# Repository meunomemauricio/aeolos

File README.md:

# Aeolus

Arduino PWM Fan Controller.

## Uploading Firmware

This projects use Platform IO. When building or uploading the firmware, it's
important to specify the build environment. This will set the proper
`MODULE_ID` value depending on the expected fan direction.

    pio run -e exhaust -t upload
    pio run -e intake -t upload

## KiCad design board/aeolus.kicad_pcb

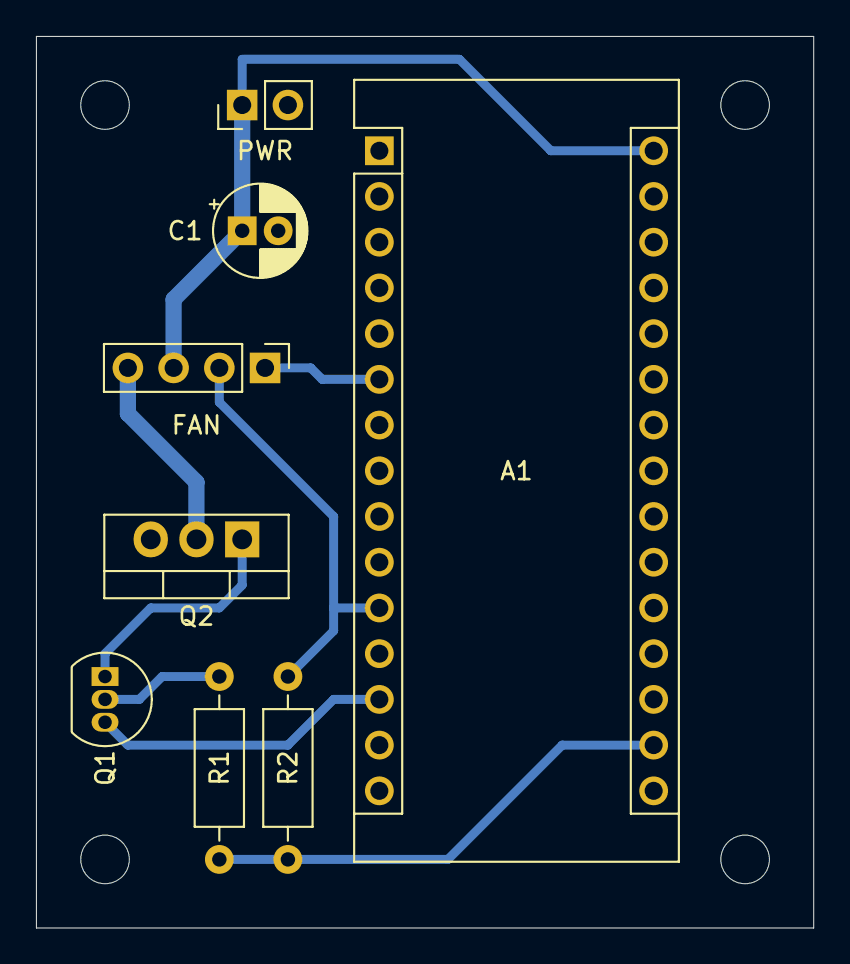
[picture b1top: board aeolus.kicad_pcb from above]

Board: 2 copper layers, 43.2 x 49.5 mm, 8 parts (0 on the bottom side), 9 nets.

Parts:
A1: Arduino_Nano_v2.x; Arduino_Nano
C1: 1uF; CP_Radial_D5.0mm_P2.00mm
FAN: Conn_01x04_Male; PinHeader_1x04_P2.54mm_Vertical
PWR: Conn_01x02_Male; PinHeader_1x02_P2.54mm_Vertical
Q1: BC549; TO-92_Inline
Q2: IRF540N; TO-220-3_Vertical
R1, R2: 10k; R_Axial_DIN0207_L6.3mm_D2.5mm_P10.16mm_Horizontal

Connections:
+3V3: A1.17, R1.1, R2.1
+12V: A1.30, C1.1, FAN.3, PWR.1
/FAN_GND: FAN.4, Q2.2
/PWM: A1.6, FAN.1
/TACH: A1.11, FAN.2, R2.2
GND: A1.29, C1.2, PWR.2, Q2.3
unnamed: A1.13, Q1.3
unnamed: Q1.1, Q2.1
unnamed: Q1.2, R1.2

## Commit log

2022-02-17 Extract from other repository
2022-02-18 Rename board and create SCAD file
2022-02-18 Project basic Setup (#1)
    * Update README
    * Extract from other repository
    * Rename board and create SCAD file
2022-02-18 Basic Fan Shape
2022-02-21 Basic fan enclosure
2022-02-21 Generate honeycomb mesh
2022-02-25 Invert Honeycomb
2022-03-03 Remove old communication
2022-03-03 Add AceButton library
2022-03-03 Specify .clang-format
2022-03-03 Revert back to cpp file
2022-03-03 Add simple button logic
2022-03-03 Adjust SP with buttons
2022-03-03 Small adjustments
2022-03-03 Create monitor GUI
2022-03-03 Remove unused code
2022-03-03 Finish monitor serial logic
2022-03-03 Start setpoint on 0
2022-03-03 Adjust controller parameters
2022-03-03 Review adjustments
2022-03-03 Button Interface and Serial Monitor app (#2)
    * Remove old communication
    * Add AceButton library
    * Specify .clang-format
    * Revert back to cpp file
    * Add simple button logic
    * Adjust SP with buttons
2022-03-03 Bump numpy from 1.16.4 to 1.21.0 in /monitor
    Bumps [numpy](https://github.com/numpy/numpy) from 1.16.4 to 1.21.0.
    - [Release notes](https://github.com/numpy/numpy/releases)
    - [Changelog](https://github.com/numpy/numpy/blob/main/doc/HOWTO_RELEASE.rst.txt)
    - [Commits](https://github.com/numpy/numpy/compare/v1.16.4...v1.21.0)
    ---
    updated-dependencies:
2022-03-04 Add a base
2022-03-04 Add electronics compartment
2022-06-22 Bump numpy from 1.16.4 to 1.22.0 in /monitor
    Bumps [numpy](https://github.com/numpy/numpy) from 1.16.4 to 1.22.0.
    - [Release notes](https://github.com/numpy/numpy/releases)
    - [Changelog](https://github.com/numpy/numpy/blob/main/doc/HOWTO_RELEASE.rst)
    - [Commits](https://github.com/numpy/numpy/compare/v1.16.4...v1.22.0)
    ---
    updated-dependencies:
